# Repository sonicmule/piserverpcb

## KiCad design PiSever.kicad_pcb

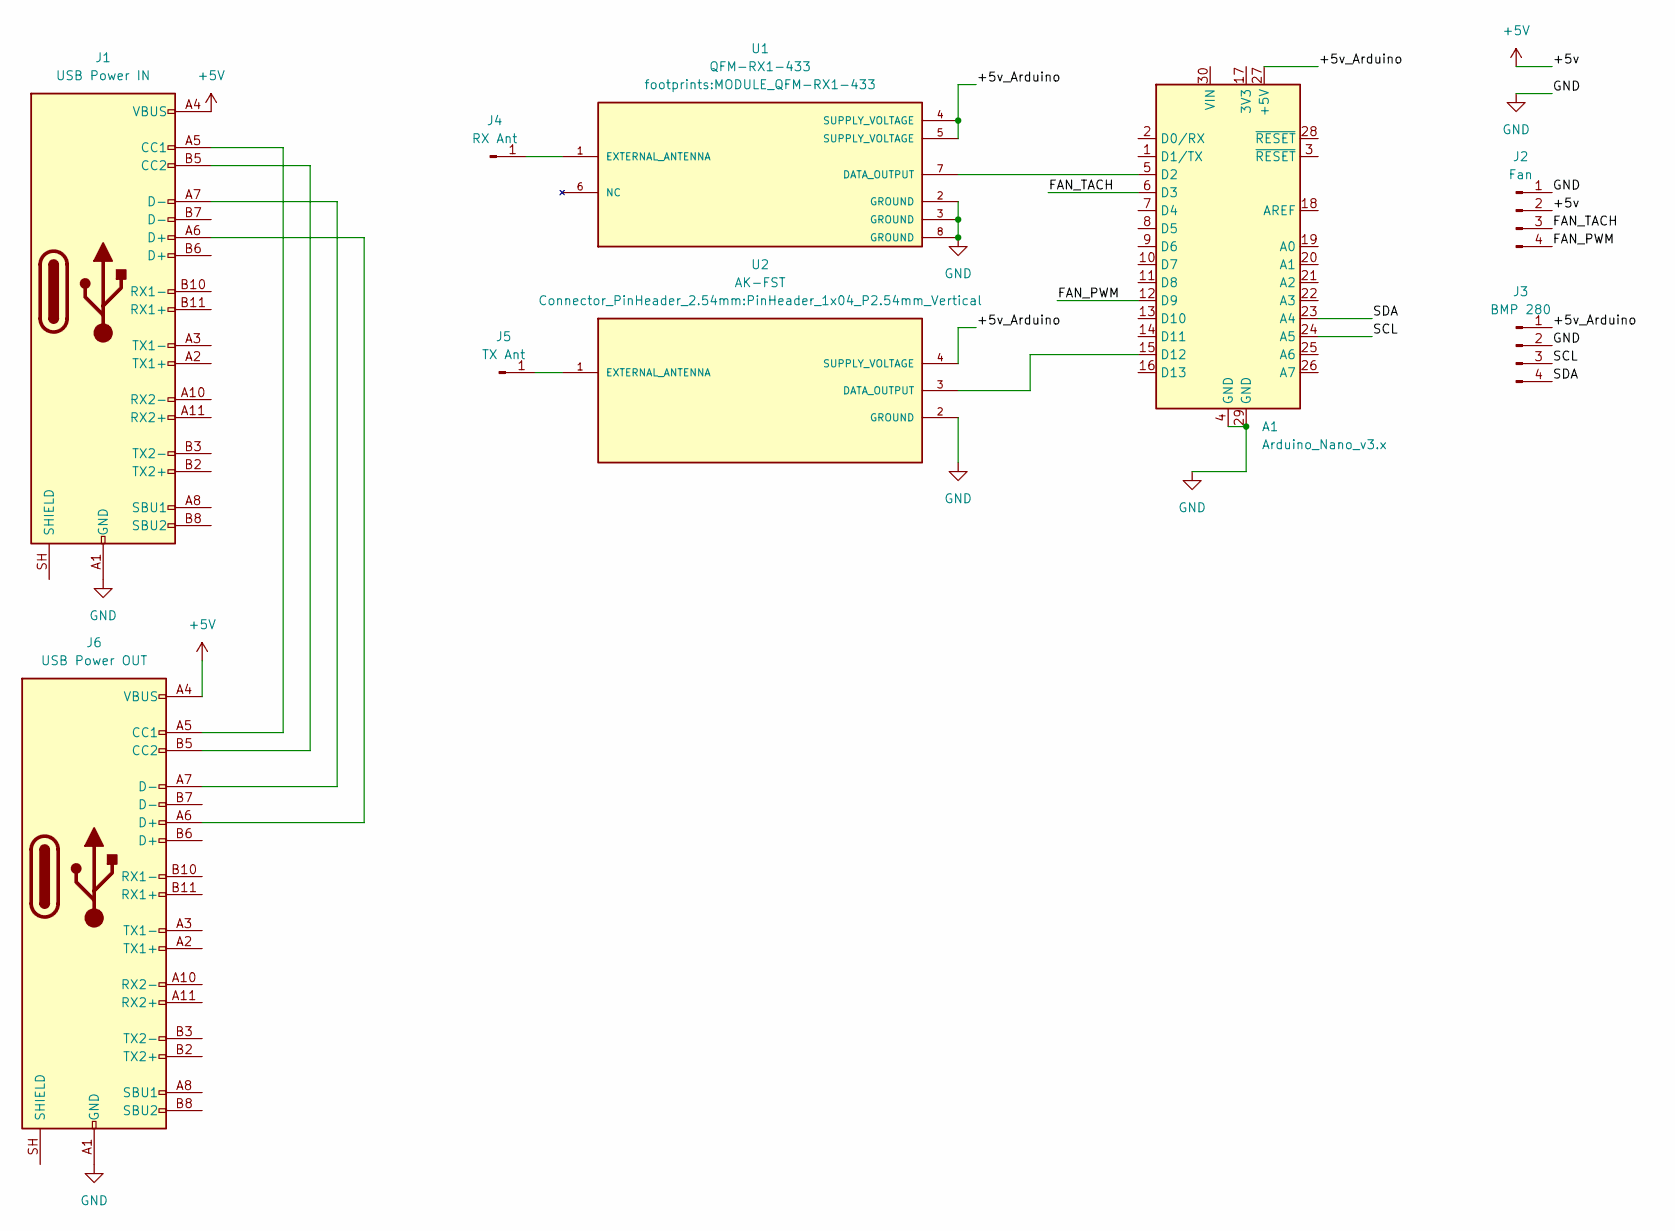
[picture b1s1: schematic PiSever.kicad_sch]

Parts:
A1: Arduino_Nano_v3.x; Arduino_Nano
J1: USB Power IN; USB_C_Receptacle_GCT_USB4085
J2: Fan; PinHeader_1x04_P2.54mm_Vertical
J3: BMP 280
J4: RX Ant; PinHeader_1x01_P2.54mm_Vertical
J5: TX Ant; PinHeader_1x01_P2.54mm_Vertical
J6: USB Power OUT; USB_C_Receptacle_GCT_USB4085
U1: QFM-RX1-433; MODULE_QFM-RX1-433; PARTREV March 14
U2: AK-FST; PinHeader_1x04_P2.54mm_Vertical; PARTREV March 14

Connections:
+5V: J1.A4 (VBUS), J1.A9 (VBUS), J1.B4 (VBUS), J1.B9 (VBUS), J2.2, J6.A4 (VBUS), J6.A9 (VBUS), J6.B4 (VBUS), J6.B9 (VBUS)
/+5v_Arduino: A1.27 (+5V), J3.1, U1.4 (SUPPLY_VOLTAGE), U1.5 (SUPPLY_VOLTAGE), U2.4 (SUPPLY_VOLTAGE)
/FAN_PWM: A1.12 (D9), J2.4
/FAN_TACH: A1.6 (D3), J2.3
/SCL: A1.24 (A5), J3.3
/SDA: A1.23 (A4), J3.4
GND: A1.4 (GND), A1.29 (GND), J1.A1 (GND), J1.A12 (GND), J1.B1 (GND), J1.B12 (GND), J2.1, J3.2, J6.A1 (GND), J6.A12 (GND), J6.B1 (GND), J6.B12 (GND), U1.2 (GROUND), U1.3 (GROUND), U1.8 (GROUND), U2.2 (GROUND)
unnamed: A1.5 (D2), U1.7 (DATA_OUTPUT)
unnamed: A1.15 (D12), U2.3 (DATA_OUTPUT)
unnamed: J1.A5 (CC1), J6.A5 (CC1)
unnamed: J1.B5 (CC2), J6.B5 (CC2)
unnamed: J1.A6 (D+), J6.A6 (D+)
unnamed: J1.A7 (D-), J6.A7 (D-)
unnamed: J4.1 (Pin_1_1), U1.1 (EXTERNAL_ANTENNA)
unnamed: J5.1 (Pin_1_1), U2.1 (EXTERNAL_ANTENNA)

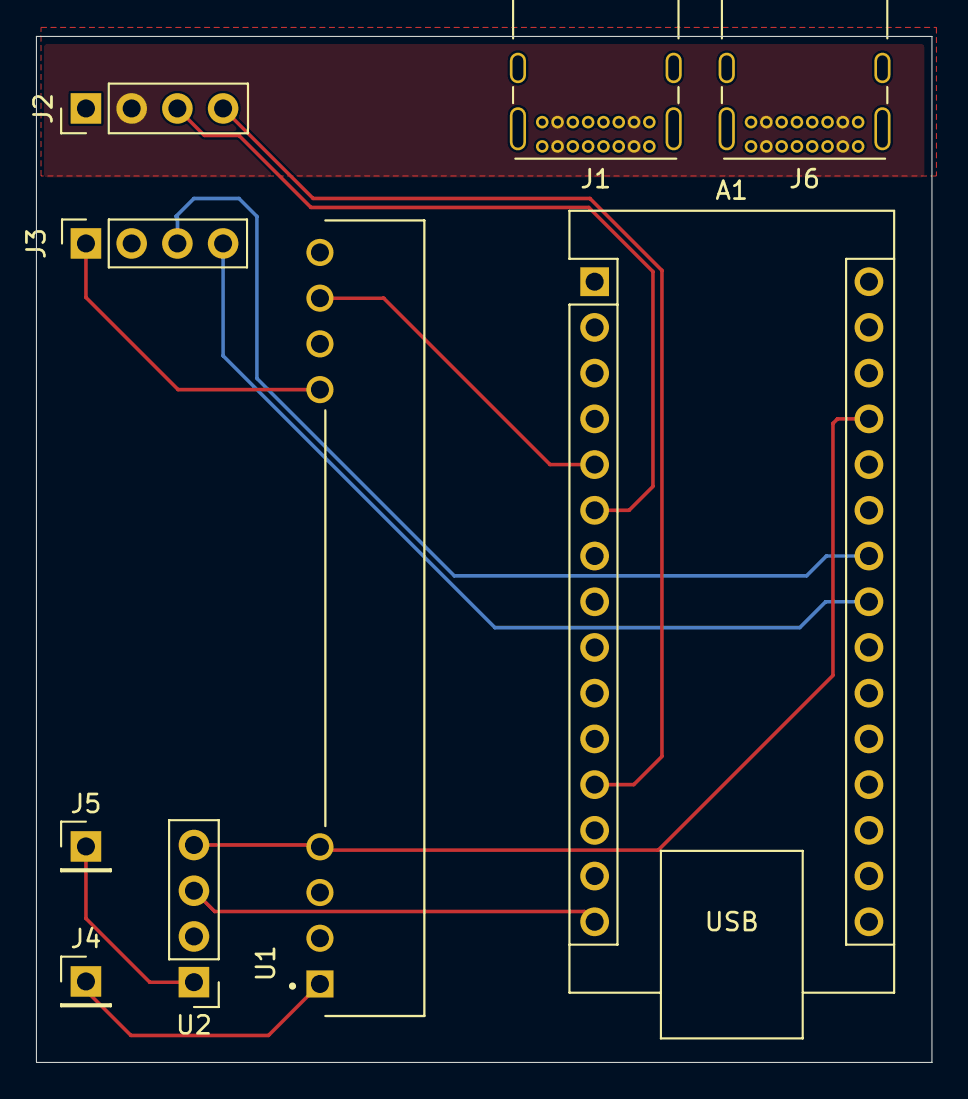
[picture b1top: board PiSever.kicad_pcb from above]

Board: 2 copper layers, 49.8 x 57.0 mm, 9 parts (0 on the bottom side), 15 nets.

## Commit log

2026-06-26 Initial create
2026-06-29 Add through hole usb
2026-06-30 Re-route
